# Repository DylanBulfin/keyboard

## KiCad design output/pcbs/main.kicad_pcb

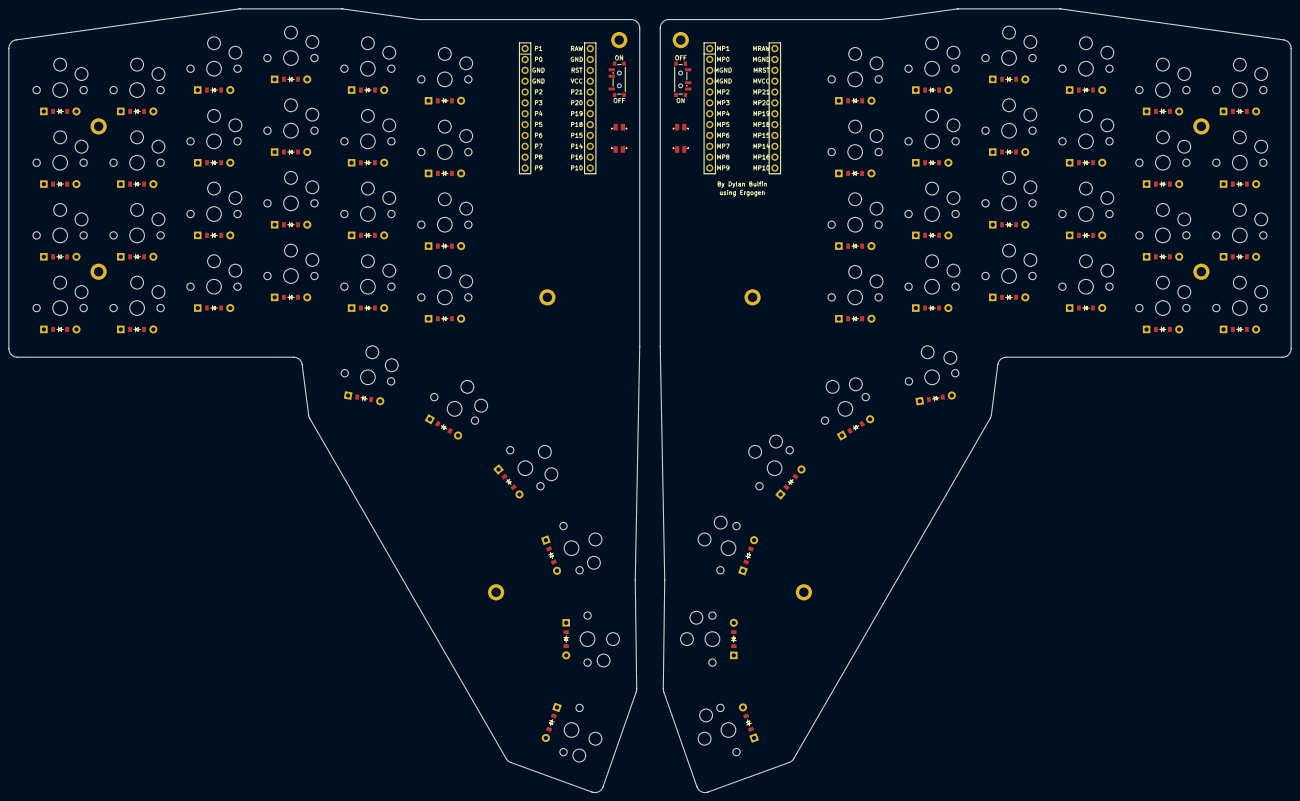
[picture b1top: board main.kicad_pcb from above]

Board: 2 copper layers, 300.0 x 183.4 mm, 136 parts (0 on the bottom side), 88 nets, no tracks yet.

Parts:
D1, D2, D3, D4, D5, D6, D7, D8, D9, D10, D11, D12, D13, D14, D15, D16, D17, D18, D19, D20, D21, D22, D23, D24, D25, D26, D27, D28, D29, D30, D31, D32, D33, D34, D35, D36, D37, D38, D39, D40, D41, D42, D43, D44, D45, D46, D47, D48, D49, D50, D51, D52, D53, D54, D55, D56, D57, D58, D59, D60: ComboDiode
H1, H2, H3, H4, H5, H6, H7, H8, H9, H10: mounting_hole_plated
MCU1, MCU2: mcu_nice_nano
PWR1, PWR2: power_switch_smd_side
RST1, RST2: reset_switch_smd_side
S1, S2, S3, S4, S5, S6, S7, S8, S9, S10, S11, S12, S13, S14, S15, S16, S17, S18, S19, S20, S21, S22, S23, S24, S25, S26, S27, S28, S29, S30, S31, S32, S33, S34, S35, S36, S37, S38, S39, S40, S41, S42, S43, S44, S45, S46, S47, S48, S49, S50, S51, S52, S53, S54, S55, S56, S57, S58, S59, S60: PG1350

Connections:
GND: MCU1.2, MCU1.21, MCU1.22, RST1.1, RST1.3
MGND: MCU2.2, MCU2.21, MCU2.22, RST2.1, RST2.3
MP7: D55.1, D56.1, D57.1, D58.1, D59.1, D60.1, MCU2.15
MP8: D31.1, D35.1, D39.1, D43.1, D47.1, D51.1, MCU2.14
MP9: D32.1, D36.1, D40.1, D44.1, D48.1, D52.1, MCU2.13
MP10: D33.1, D37.1, D41.1, D45.1, D49.1, D53.1, MCU2.12
MP14: MCU2.10, S51.1, S52.1, S53.1, S54.1, S60.1
MP15: MCU2.9, S47.1, S48.1, S49.1, S50.1, S59.1
MP16: D34.1, D38.1, D42.1, D46.1, D50.1, D54.1, MCU2.11
MP18: MCU2.8, S43.1, S44.1, S45.1, S46.1, S58.1
MP19: MCU2.7, S39.1, S40.1, S41.1, S42.1, S57.1
MP20: MCU2.6, S35.1, S36.1, S37.1, S38.1, S56.1
MP21: MCU2.5, S31.1, S32.1, S33.1, S34.1, S55.1
MRAW: MCU2.1, PWR2.2
MRST: MCU2.3, RST2.2, RST2.4
P2: MCU1.20, S1.1, S2.1, S3.1, S4.1, S25.1
P3: MCU1.19, S5.1, S6.1, S7.1, S8.1, S26.1
P4: MCU1.18, S9.1, S10.1, S11.1, S12.1, S27.1
P5: MCU1.17, S13.1, S14.1, S15.1, S16.1, S28.1
P6: MCU1.16, S17.1, S18.1, S19.1, S20.1, S29.1
P7: MCU1.15, S21.1, S22.1, S23.1, S24.1, S30.1
P8: D4.1, D8.1, D12.1, D16.1, D20.1, D24.1, MCU1.14
P9: D3.1, D7.1, D11.1, D15.1, D19.1, D23.1, MCU1.13
P10: D2.1, D6.1, D10.1, D14.1, D18.1, D22.1, MCU1.12
P14: D25.1, D26.1, D27.1, D28.1, D29.1, D30.1, MCU1.10
P16: D1.1, D5.1, D9.1, D13.1, D17.1, D21.1, MCU1.11
RAW: MCU1.1, PWR1.2
RST: MCU1.3, RST1.2, RST1.4
fifth_cluster: D29.2, S29.2
first_cluster: D25.2, S25.2
fourth_cluster: D28.2, S28.2
index_bottom: D17.2, S17.2
index_home: D18.2, S18.2
index_num: D20.2, S20.2
index_top: D19.2, S19.2
inner_bottom: D21.2, S21.2
inner_home: D22.2, S22.2
inner_num: D24.2, S24.2
inner_top: D23.2, S23.2
middle_bottom: D13.2, S13.2
middle_home: D14.2, S14.2
middle_num: D16.2, S16.2
middle_top: D15.2, S15.2
mirror_fifth_cluster: D59.2, S59.2
mirror_first_cluster: D55.2, S55.2
mirror_fourth_cluster: D58.2, S58.2
mirror_index_bottom: D47.2, S47.2
mirror_index_home: D48.2, S48.2
mirror_index_num: D50.2, S50.2
mirror_index_top: D49.2, S49.2
mirror_inner_bottom: D51.2, S51.2
mirror_inner_home: D52.2, S52.2
mirror_inner_num: D54.2, S54.2
mirror_inner_top: D53.2, S53.2
mirror_middle_bottom: D43.2, S43.2
mirror_middle_home: D44.2, S44.2
mirror_middle_num: D46.2, S46.2
mirror_middle_top: D45.2, S45.2
mirror_outer_bottom: D31.2, S31.2
mirror_outer_home: D32.2, S32.2
mirror_outer_num: D34.2, S34.2
mirror_outer_top: D33.2, S33.2
mirror_pinky_bottom: D35.2, S35.2
mirror_pinky_home: D36.2, S36.2
mirror_pinky_num: D38.2, S38.2
mirror_pinky_top: D37.2, S37.2
mirror_ring_bottom: D39.2, S39.2
mirror_ring_home: D40.2, S40.2
mirror_ring_num: D42.2, S42.2
mirror_ring_top: D41.2, S41.2
mirror_second_cluster: D56.2, S56.2
mirror_sixth_cluster: D60.2, S60.2
mirror_third_cluster: D57.2, S57.2
outer_bottom: D1.2, S1.2
outer_home: D2.2, S2.2
outer_num: D4.2, S4.2
outer_top: D3.2, S3.2
pinky_bottom: D5.2, S5.2
pinky_home: D6.2, S6.2
pinky_num: D8.2, S8.2
pinky_top: D7.2, S7.2
ring_bottom: D9.2, S9.2
ring_home: D10.2, S10.2
ring_num: D12.2, S12.2
ring_top: D11.2, S11.2
second_cluster: D26.2, S26.2
sixth_cluster: D30.2, S30.2
third_cluster: D27.2, S27.2

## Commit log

2025-05-03 Initial commit, basic left hand outlines + pcb with row/col nets
2025-05-03 Fix state
2025-05-03 Fix reset position, nets
2025-05-03 Nearly viable product
2025-05-03 Updating footprints/placement
2025-05-03 Finished left half maybe
2025-05-04 Start adding mirrored right layer with alternate nets
2025-05-04 Adding mounting holes
2025-05-04 Add attribution
2025-05-04 Removing logo
2025-05-04 Route diodes, switches
2025-05-04 Finish wiring
2025-05-04 Change template for pcb
2025-05-04 Fix net names
2025-05-04 Start (hopefully final) pass
2025-05-04 Finish switch-local wiring
2025-05-04 Matrix column wiring
2025-05-04 Fix DRC, add copper fills + vias to connect isolated fills
2025-05-05 Splitting pcb for fabrication
2025-05-05 Fill out case code, get converted stls
